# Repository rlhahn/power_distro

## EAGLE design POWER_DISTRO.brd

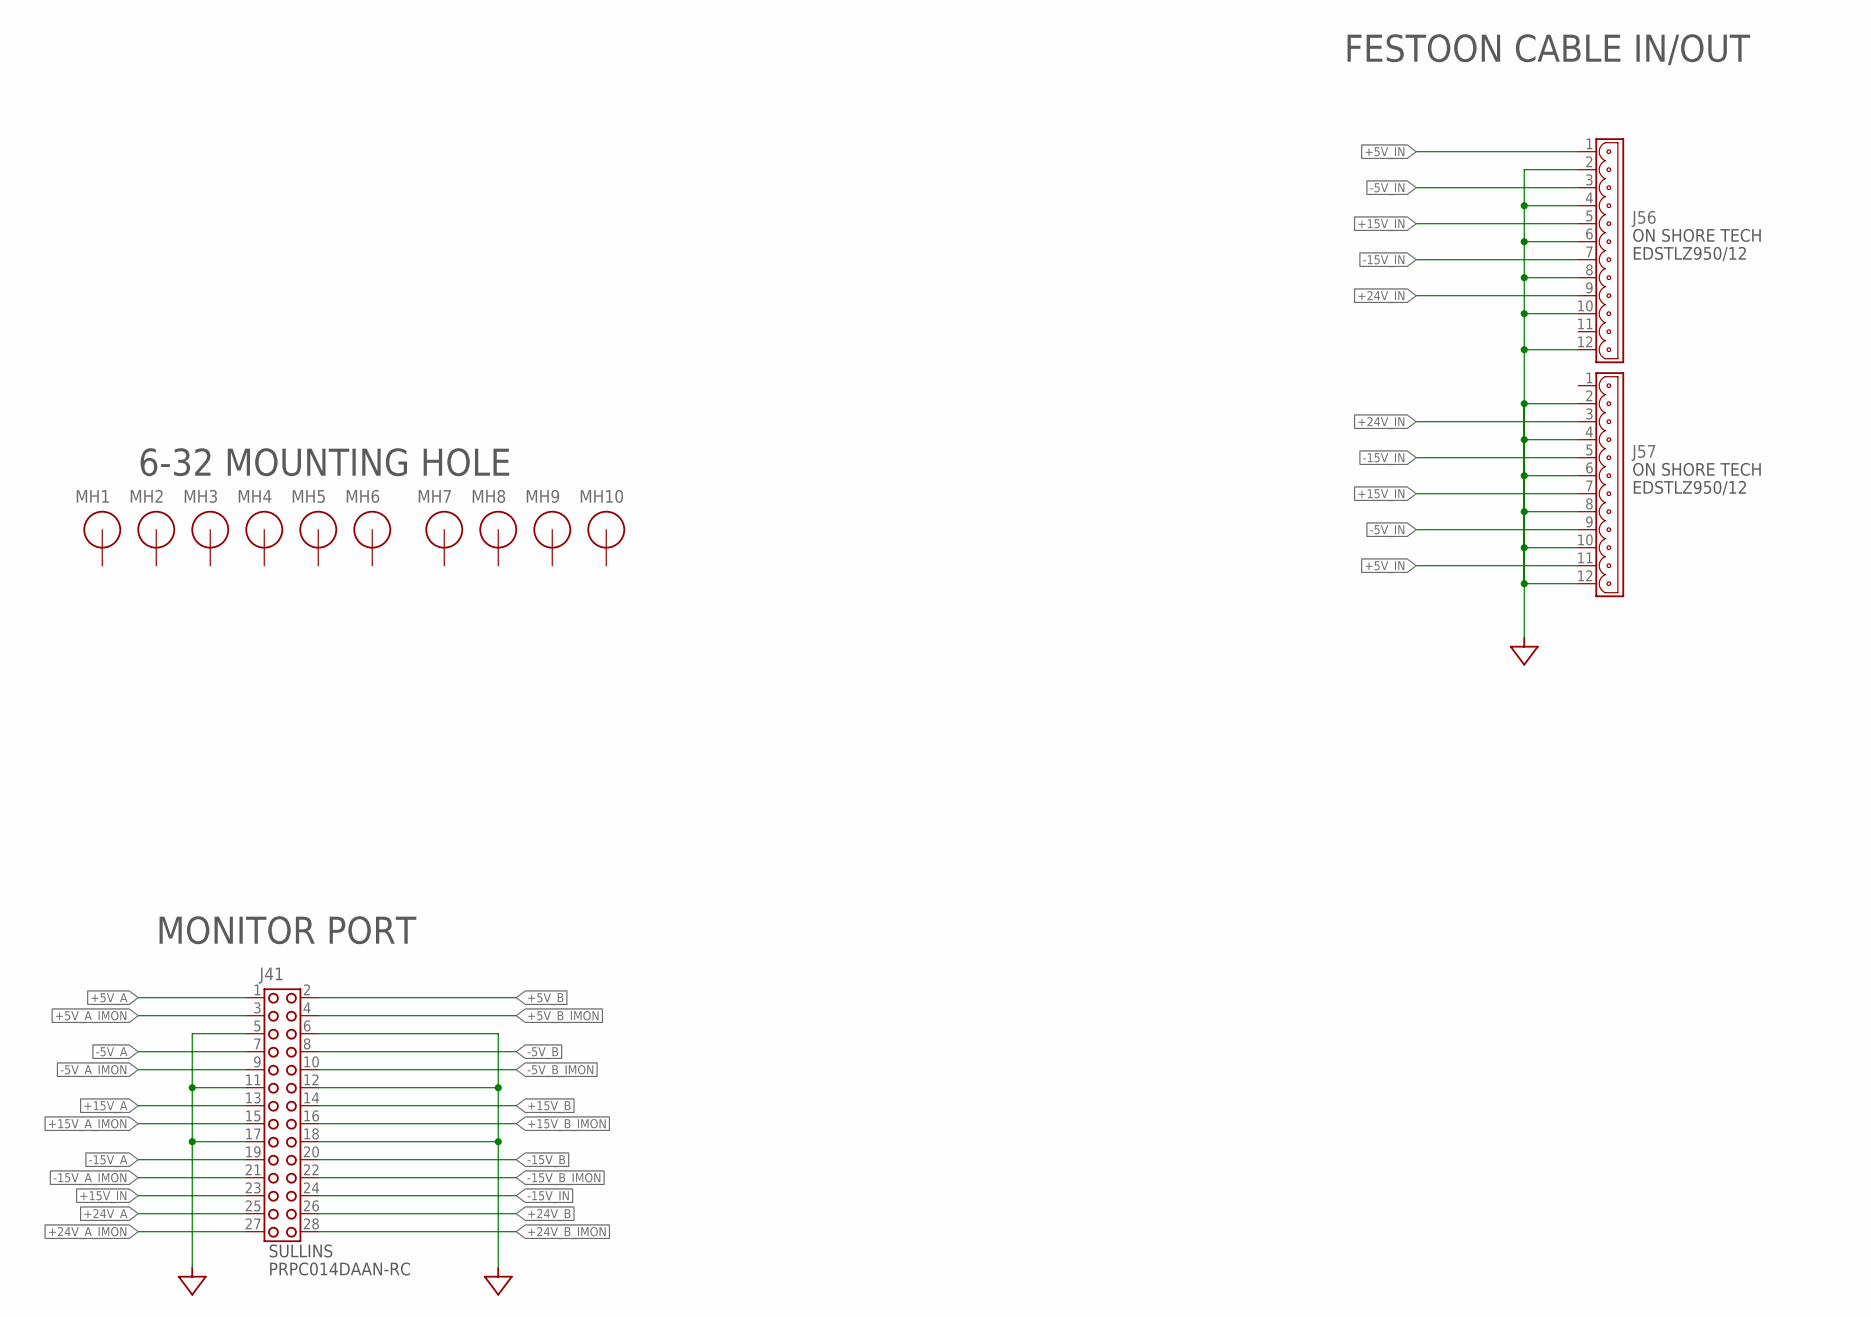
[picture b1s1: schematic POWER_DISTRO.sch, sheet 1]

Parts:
J41: HDR_2X14X100; 2X14X0.100_HDR
J56, J57: CONN_SCREWTERM_5.08MM_12POS; OST_OSTTJ125153
MH1, MH2, MH3, MH4, MH5, MH6, MH7, MH8, MH9, MH10: MTG-HOLE-6-32; MTG-6-32

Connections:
+5V_A: J41.1; also elsewhere on the board
+5V_A_IMON: J41.3; also elsewhere on the board
+5V_B: J41.2; also elsewhere on the board
+5V_B_IMON: J41.4; also elsewhere on the board
+5V_IN: J56.1, J57.11; also elsewhere on the board
+15V_A: J41.13; also elsewhere on the board
+15V_A_IMON: J41.15; also elsewhere on the board
+15V_B: J41.14; also elsewhere on the board
+15V_B_IMON: J41.16; also elsewhere on the board
+15V_IN: J41.23, J56.5, J57.7; also elsewhere on the board
+24V_A: J41.25; also elsewhere on the board
+24V_A_IMON: J41.27; also elsewhere on the board
+24V_B: J41.26; also elsewhere on the board
+24V_B_IMON: J41.28; also elsewhere on the board
+24V_IN: J56.9, J57.3; also elsewhere on the board
-5V_A: J41.7; also elsewhere on the board
-5V_A_IMON: J41.9; also elsewhere on the board
-5V_B: J41.8; also elsewhere on the board
-5V_B_IMON: J41.10; also elsewhere on the board
-5V_IN: J56.3, J57.9; also elsewhere on the board
-15V_A: J41.19; also elsewhere on the board
-15V_A_IMON: J41.21; also elsewhere on the board
-15V_B: J41.20; also elsewhere on the board
-15V_B_IMON: J41.22; also elsewhere on the board
-15V_IN: J41.24, J56.7, J57.5; also elsewhere on the board
AGND: J41.5, J41.6, J41.11, J41.12, J41.17, J41.18, J56.2, J56.4, J56.6, J56.8, J56.10, J56.12, J57.2, J57.4, J57.6, J57.8, J57.10, J57.12; also elsewhere on the board

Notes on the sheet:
6-32 MOUNTING HOLE
MONITOR PORT
FESTOON CABLE IN/OUT

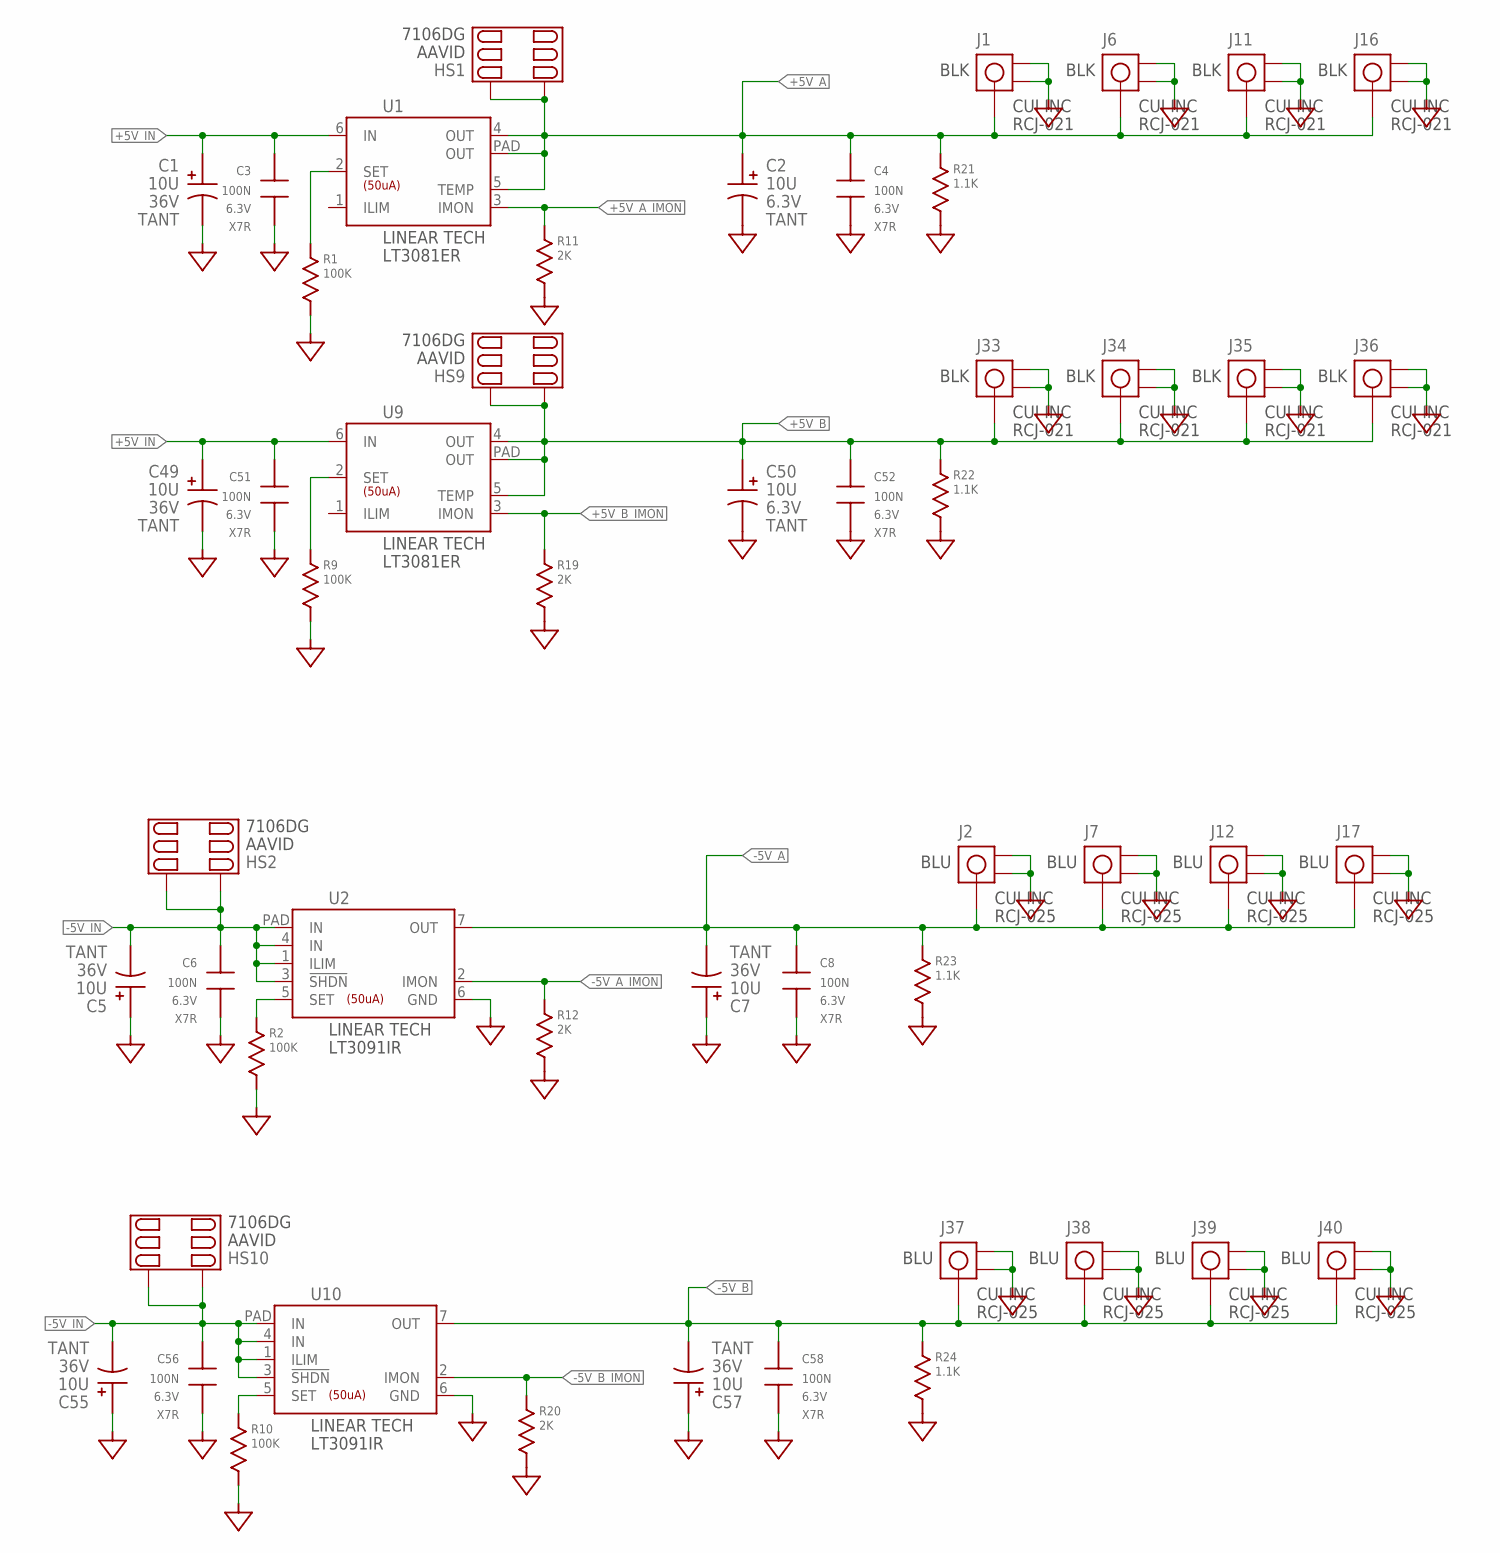
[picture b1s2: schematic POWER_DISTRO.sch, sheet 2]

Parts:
C1, C5, C7, C49, C55, C57: 10U; CAP-SIZE_D/E_EIA7343; VOLTAGE 36V
C2, C50: 10U; CAP-SIZE_D/E_EIA7343
C3, C4, C6, C8, C51, C52, C56, C58: 100N; R-0805
HS1, HS2, HS9, HS10: HEATSINK_AAVID_7106; AAVID_7106
J1, J2, J6, J7, J11, J12, J16, J17, J33, J34, J35, J36, J37, J38, J39, J40: CONN_RCA; CUI_RCJ-02X
R1, R2, R9, R10: 100K; R-0805
R11, R12, R20: 2K; R-0805
R19: 2K; R-0805; TOLERANCE 1%
R21, R22, R23, R24: 1.1K; R-0805
U1, U9: REG_LT3081; DD-7_LINEARTECH
U2, U10: REG_LT3091; DD-7_LINEARTECH

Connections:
+5V_A: C2.+, C4.A, HS1.L, HS1.R, J1.PIN, J6.PIN, J11.PIN, J16.PIN, R21.A, U1.4 (OUT), U1.5 (TEMP), U1.PAD (OUT); also elsewhere on the board
+5V_A_IMON: R11.A, U1.3 (IMON); also elsewhere on the board
+5V_B: C50.+, C52.A, HS9.L, HS9.R, J33.PIN, J34.PIN, J35.PIN, J36.PIN, R22.A, U9.4 (OUT), U9.5 (TEMP), U9.PAD (OUT); also elsewhere on the board
+5V_B_IMON: R19.A, U9.3 (IMON); also elsewhere on the board
+5V_IN: C1.+, C3.A, C49.+, C51.A, U1.6 (IN), U9.6 (IN); also elsewhere on the board
-5V_A: C7.-, C8.A, J2.PIN, J7.PIN, J12.PIN, J17.PIN, R23.A, U2.7 (OUT); also elsewhere on the board
-5V_A_IMON: R12.A, U2.2 (IMON); also elsewhere on the board
-5V_B: C57.-, C58.A, J37.PIN, J38.PIN, J39.PIN, J40.PIN, R24.A, U10.7 (OUT); also elsewhere on the board
-5V_B_IMON: R20.A, U10.2 (IMON); also elsewhere on the board
-5V_IN: C5.-, C6.A, C55.-, C56.A, HS2.L, HS2.R, HS10.L, HS10.R, U2.1 (ILIM), U2.3 (!SHDN), U2.4 (IN), U2.PAD (IN), U10.1 (ILIM), U10.3 (!SHDN), U10.4 (IN), U10.PAD (IN); also elsewhere on the board
AGND: C1.-, C2.-, C3.B, C4.B, C5.+, C6.B, C7.+, C8.B, C49.-, C50.-, C51.B, C52.B, C55.+, C56.B, C57.+, C58.B, J1.GND@1, J1.GND@2, J2.GND@1, J2.GND@2, J6.GND@1, J6.GND@2, J7.GND@1, J7.GND@2, J11.GND@1, J11.GND@2, J12.GND@1, J12.GND@2, J16.GND@1, J16.GND@2, J17.GND@1, J17.GND@2, J33.GND@1, J33.GND@2, J34.GND@1, J34.GND@2, J35.GND@1, J35.GND@2, J36.GND@1, J36.GND@2, J37.GND@1, J37.GND@2, J38.GND@1, J38.GND@2, J39.GND@1, J39.GND@2, J40.GND@1, J40.GND@2, R1.B, R2.B, R9.B, R10.B, R11.B, R12.B, R19.B, R20.B, R21.B, R22.B, R23.B, R24.B, U2.6 (GND), U10.6 (GND); also elsewhere on the board
unnamed: R1.A, U1.2 (SET)
unnamed: R2.A, U2.5 (SET)
unnamed: R9.A, U9.2 (SET)
unnamed: R10.A, U10.5 (SET)

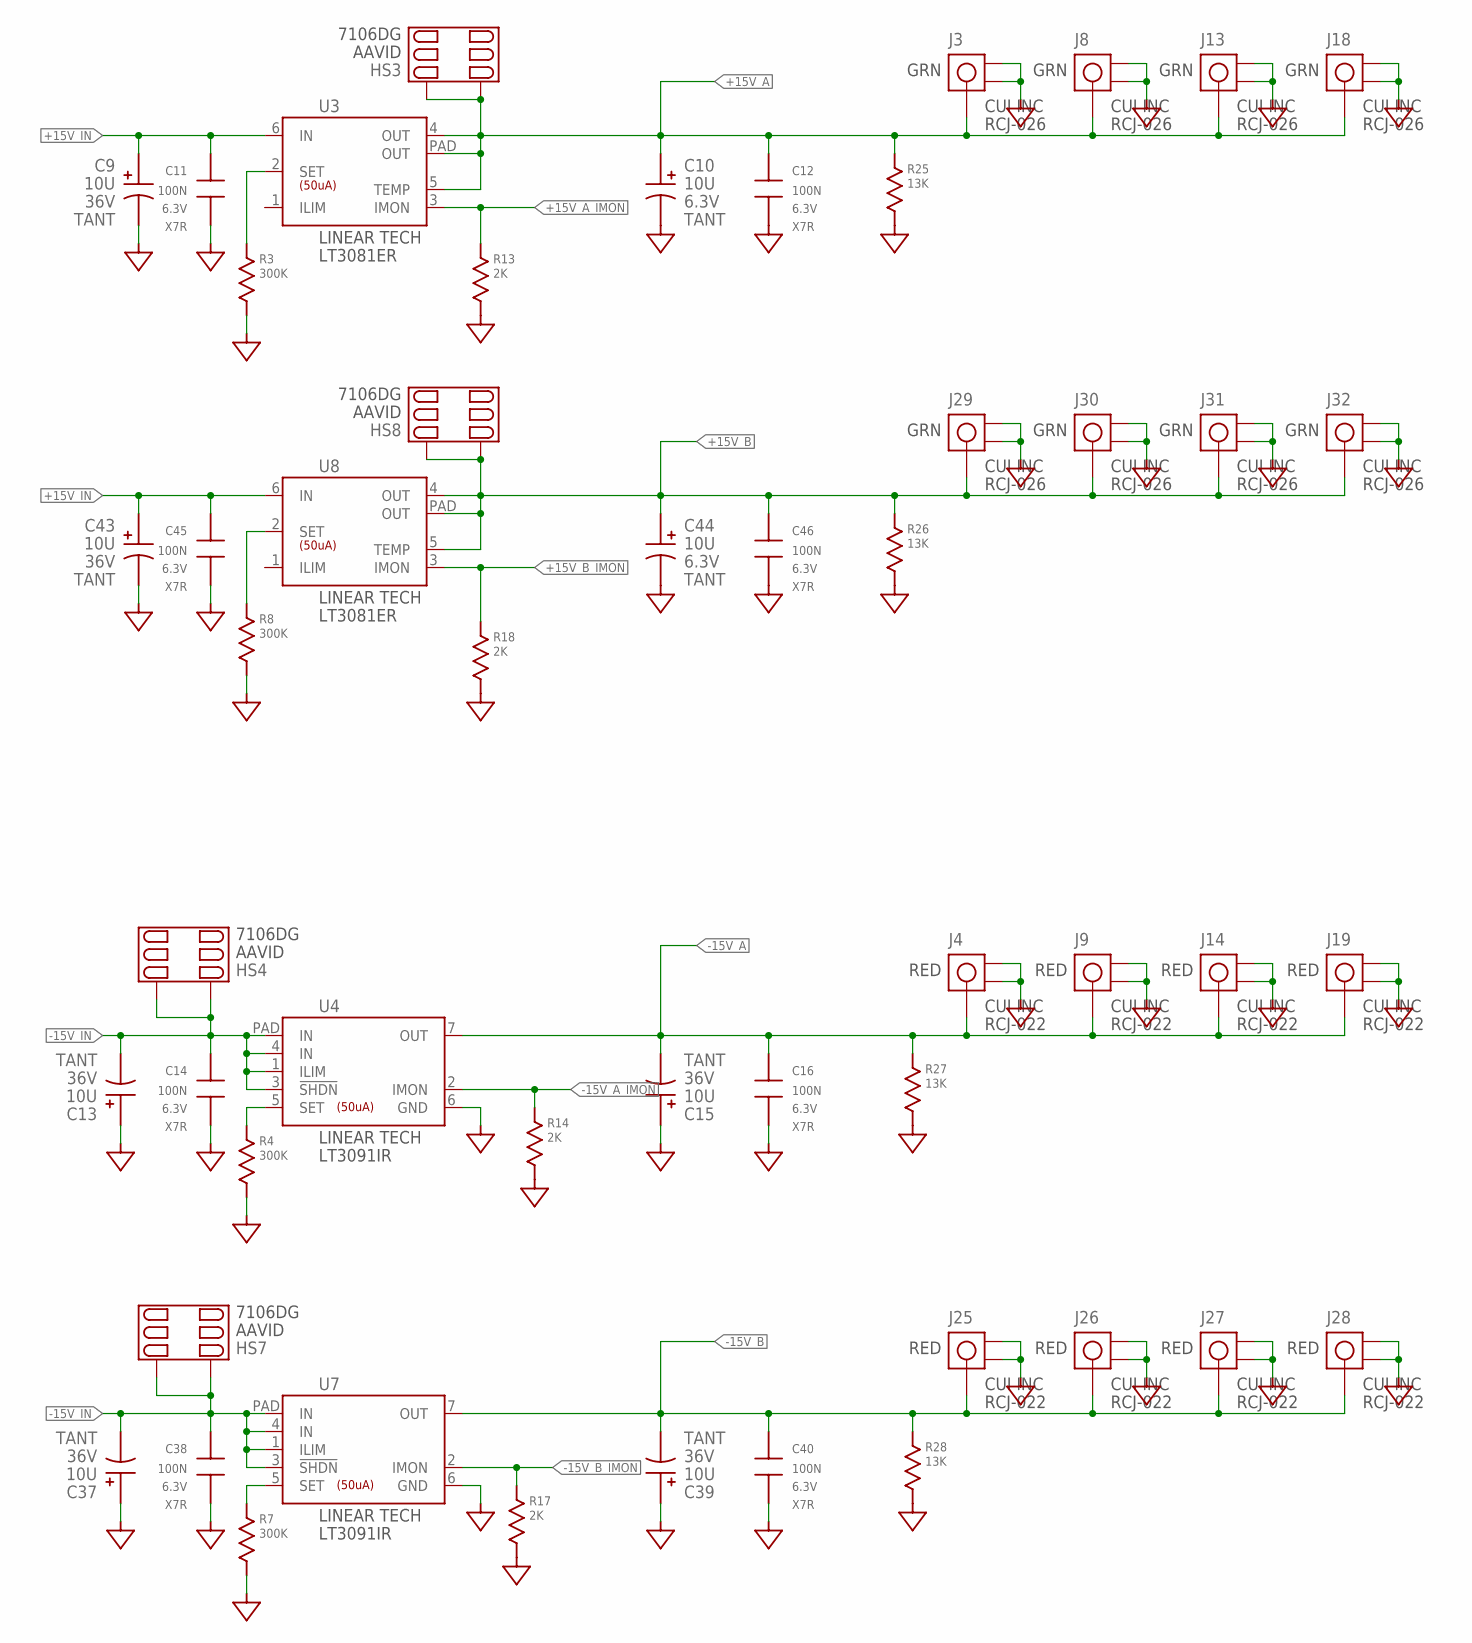
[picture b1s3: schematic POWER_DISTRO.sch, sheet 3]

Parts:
C9, C13, C15, C37, C39, C43: 10U; CAP-SIZE_D/E_EIA7343; VOLTAGE 36V
C10, C44: 10U; CAP-SIZE_D/E_EIA7343
C11, C12, C14, C16, C38, C40, C45, C46: 100N; R-0805
HS3, HS4, HS7, HS8: HEATSINK_AAVID_7106; AAVID_7106
J3, J4, J8, J9, J13, J14, J18, J19, J25, J26, J27, J28, J29, J30, J31, J32: CONN_RCA; CUI_RCJ-02X
R3, R4, R7, R8: 300K; R-0805
R13, R14, R17, R18: 2K; R-0805; TOLERANCE 1%
R25, R26, R27, R28: 13K; R-0805; TOLERANCE 1%
U3, U8: REG_LT3081; DD-7_LINEARTECH
U4, U7: REG_LT3091; DD-7_LINEARTECH

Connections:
+15V_A: C10.+, C12.A, HS3.L, HS3.R, J3.PIN, J8.PIN, J13.PIN, J18.PIN, R25.A, U3.4 (OUT), U3.5 (TEMP), U3.PAD (OUT); also elsewhere on the board
+15V_A_IMON: R13.A, U3.3 (IMON); also elsewhere on the board
+15V_B: C44.+, C46.A, HS8.L, HS8.R, J29.PIN, J30.PIN, J31.PIN, J32.PIN, R26.A, U8.4 (OUT), U8.5 (TEMP), U8.PAD (OUT); also elsewhere on the board
+15V_B_IMON: R18.A, U8.3 (IMON); also elsewhere on the board
+15V_IN: C9.+, C11.A, C43.+, C45.A, U3.6 (IN), U8.6 (IN); also elsewhere on the board
-15V_A: C15.-, C16.A, J4.PIN, J9.PIN, J14.PIN, J19.PIN, R27.A, U4.7 (OUT); also elsewhere on the board
-15V_A_IMON: R14.A, U4.2 (IMON); also elsewhere on the board
-15V_B: C39.-, C40.A, J25.PIN, J26.PIN, J27.PIN, J28.PIN, R28.A, U7.7 (OUT); also elsewhere on the board
-15V_B_IMON: R17.A, U7.2 (IMON); also elsewhere on the board
-15V_IN: C13.-, C14.A, C37.-, C38.A, HS4.L, HS4.R, HS7.L, HS7.R, U4.1 (ILIM), U4.3 (!SHDN), U4.4 (IN), U4.PAD (IN), U7.1 (ILIM), U7.3 (!SHDN), U7.4 (IN), U7.PAD (IN); also elsewhere on the board
AGND: C9.-, C10.-, C11.B, C12.B, C13.+, C14.B, C15.+, C16.B, C37.+, C38.B, C39.+, C40.B, C43.-, C44.-, C45.B, C46.B, J3.GND@1, J3.GND@2, J4.GND@1, J4.GND@2, J8.GND@1, J8.GND@2, J9.GND@1, J9.GND@2, J13.GND@1, J13.GND@2, J14.GND@1, J14.GND@2, J18.GND@1, J18.GND@2, J19.GND@1, J19.GND@2, J25.GND@1, J25.GND@2, J26.GND@1, J26.GND@2, J27.GND@1, J27.GND@2, J28.GND@1, J28.GND@2, J29.GND@1, J29.GND@2, J30.GND@1, J30.GND@2, J31.GND@1, J31.GND@2, J32.GND@1, J32.GND@2, R3.B, R4.B, R7.B, R8.B, R13.B, R14.B, R17.B, R18.B, R25.B, R26.B, R27.B, R28.B, U4.6 (GND), U7.6 (GND); also elsewhere on the board
unnamed: R3.A, U3.2 (SET)
unnamed: R4.A, U4.5 (SET)
unnamed: R7.A, U7.5 (SET)
unnamed: R8.A, U8.2 (SET)

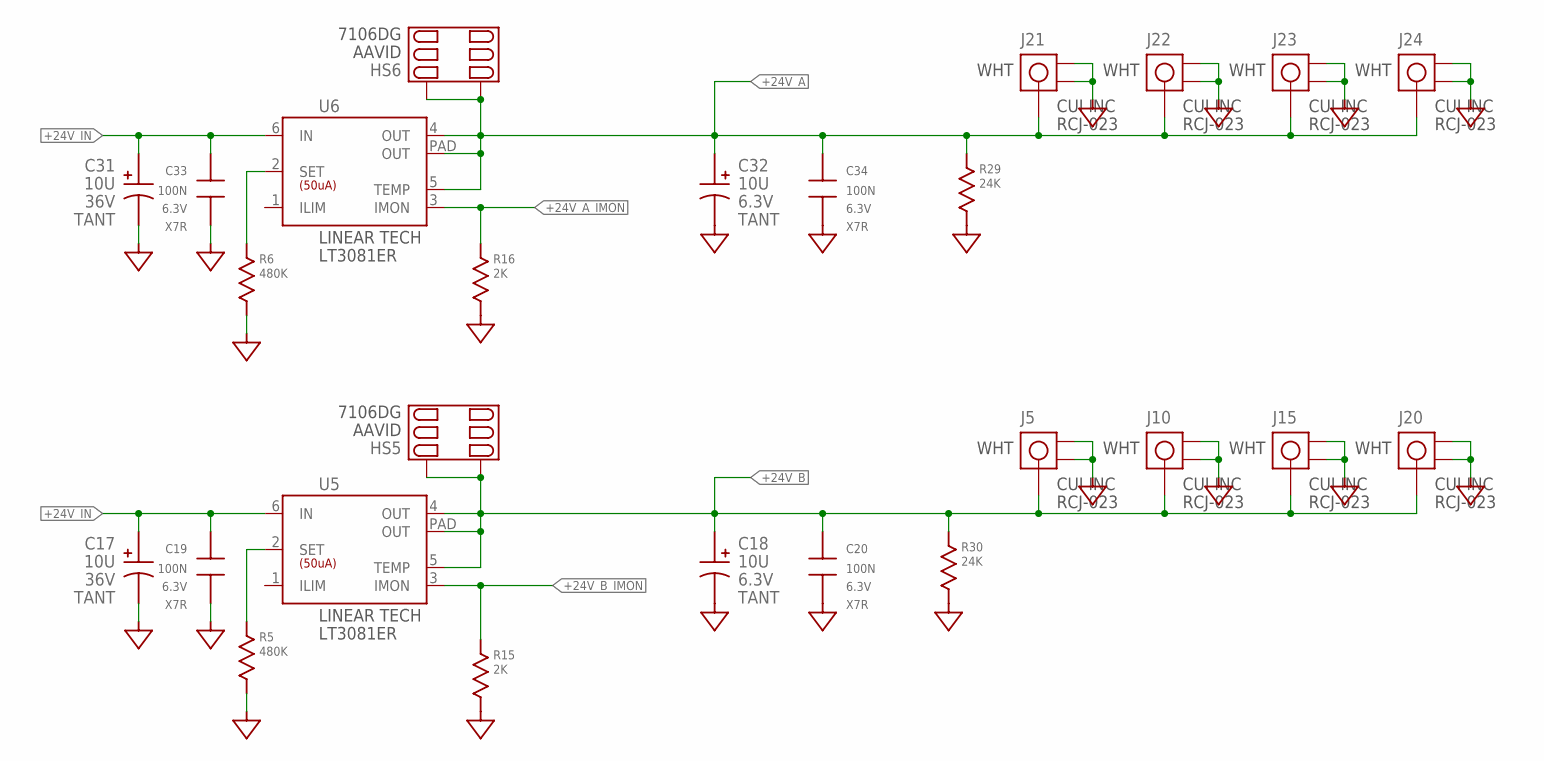
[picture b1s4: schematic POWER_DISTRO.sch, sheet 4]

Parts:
C17, C31: 10U; CAP-SIZE_D/E_EIA7343; VOLTAGE 36V
C18, C32: 10U; CAP-SIZE_D/E_EIA7343
C19, C20, C33, C34: 100N; R-0805
HS5, HS6: HEATSINK_AAVID_7106; AAVID_7106
J5, J10, J15, J20, J21, J22, J23, J24: CONN_RCA; CUI_RCJ-02X
R5, R6: 480K; R-0805
R15, R16: 2K; R-0805; TOLERANCE 1%
R29, R30: 24K; R-0805; TOLERANCE 1%
U5, U6: REG_LT3081; DD-7_LINEARTECH

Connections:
+24V_A: C32.+, C34.A, HS6.L, HS6.R, J21.PIN, J22.PIN, J23.PIN, J24.PIN, R29.A, U6.4 (OUT), U6.5 (TEMP), U6.PAD (OUT); also elsewhere on the board
+24V_A_IMON: R16.A, U6.3 (IMON); also elsewhere on the board
+24V_B: C18.+, C20.A, HS5.L, HS5.R, J5.PIN, J10.PIN, J15.PIN, J20.PIN, R30.A, U5.4 (OUT), U5.5 (TEMP), U5.PAD (OUT); also elsewhere on the board
+24V_B_IMON: R15.A, U5.3 (IMON); also elsewhere on the board
+24V_IN: C17.+, C19.A, C31.+, C33.A, U5.6 (IN), U6.6 (IN); also elsewhere on the board
AGND: C17.-, C18.-, C19.B, C20.B, C31.-, C32.-, C33.B, C34.B, J5.GND@1, J5.GND@2, J10.GND@1, J10.GND@2, J15.GND@1, J15.GND@2, J20.GND@1, J20.GND@2, J21.GND@1, J21.GND@2, J22.GND@1, J22.GND@2, J23.GND@1, J23.GND@2, J24.GND@1, J24.GND@2, R5.B, R6.B, R15.B, R16.B, R29.B, R30.B; also elsewhere on the board
unnamed: R5.A, U5.2 (SET)
unnamed: R6.A, U6.2 (SET)

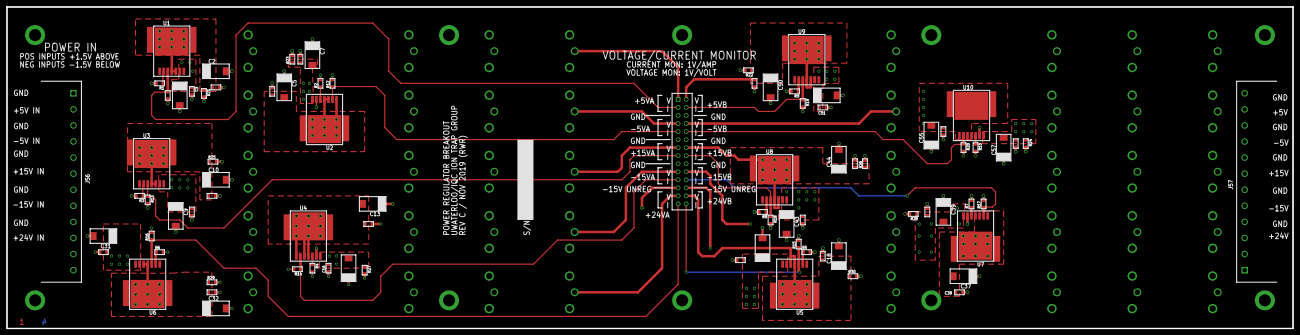
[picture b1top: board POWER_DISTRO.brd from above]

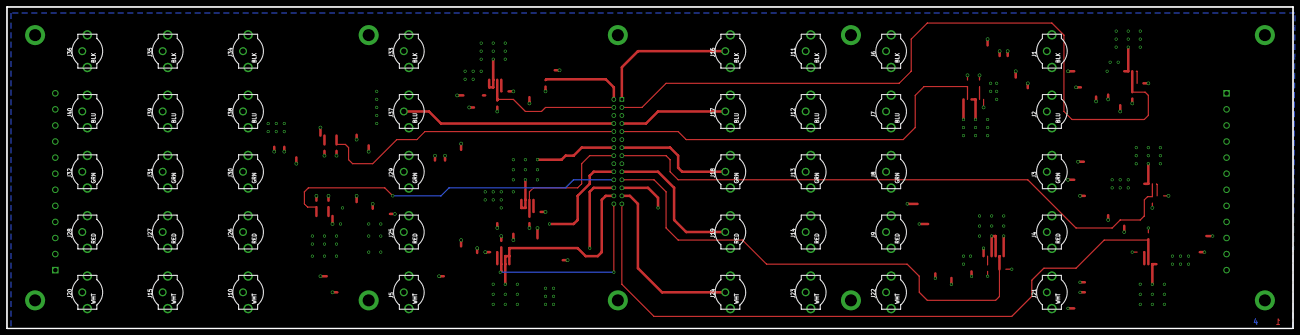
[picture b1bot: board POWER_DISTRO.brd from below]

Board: 4 copper layers, 406.4 x 101.6 mm, 143 parts (40 on the bottom side), 36 nets.

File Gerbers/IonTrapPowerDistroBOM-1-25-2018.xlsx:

Ion Trap Power Distro Box Bill Of Materials (1-25-2018)
QTY | REF | PACKAGE | VALUE | COLOR | COST | DIELECTRIC | MFG | MPN | PACKAGE | PRICE | TOLERANCE | VENDOR | VOLTAGE | VPN
14 | C1,C5,C7,C9,C13,C15,C17,C31,C37,C39,C43,C49,C55,C57, | CAP-SIZE_D/E_EIA7343 | 10U |  | 1.5 | TANT | AVX | TAJD-SERIES |  |  |  | DIGIKEY | 36V
6 | C2,C10,C18,C32,C44,C50, | CAP-SIZE_D/E_EIA7343 | 10U |  | 1.5 | TANT | AVX | TAJD-SERIES |  |  |  | DIGIKEY | 6.3V
20 | C3,C4,C6,C8,C11,C12,C14,C16,C19,C20,C33,C34,C38,C40,C45,C46,C51,C52,C56,C58, | R-0805 | 100N |  | 7.3999999999999996E-2 | X7R |  |  |  |  |  |  | 6.3V
10 | HS1,HS2,HS3,HS4,HS5,HS6,HS7,HS8,HS9,HS10, | AAVID_7106 | HEATSINK_AAVID_7106 |  |  |  | AAVID | 7106DG |  | 1.44 |  | DIGIKEY |  | HS412-ND
8 | J1,J6,J11,J16,J33,J34,J35,J36, | CUI_RCJ-02X | CONN_RCA | BLK |  |  | CUI INC | RCJ-021 |  | 0.88 |  | DIGIKEY |  | CP-1406-ND
8 | J2,J7,J12,J17,J37,J38,J39,J40, | CUI_RCJ-02X | CONN_RCA | BLU |  |  | CUI INC | RCJ-025 |  | 0.88 |  | DIGIKEY |  | CP-1410-ND
8 | J3,J8,J13,J18,J29,J30,J31,J32, | CUI_RCJ-02X | CONN_RCA | GRN |  |  | CUI INC | RCJ-026 |  | 0.88 |  | DIGIKEY |  | CP-1411-ND
8 | J4,J9,J14,J19,J25,J26,J27,J28, | CUI_RCJ-02X | CONN_RCA | RED |  |  | CUI INC | RCJ-022 |  | 0.88 |  | DIGIKEY |  | CP-1407-ND
8 | J5,J10,J15,J20,J21,J22,J23,J24, | CUI_RCJ-02X | CONN_RCA | WHT |  |  | CUI INC | RCJ-023 |  | 0.88 |  | DIGIKEY |  | CP-1408-ND
1 | J41, | 2X14X0.100_HDR | HDR_2X14X100 |  |  |  | SULLINS | PRPC014DAAN-RC |  | 1 |  | DIGIKEY |  | S2011EC-14-ND
6 | J46,J47,J48,J49,J50,J51, | OST_SCREWTERM_3.5MM_2POS | CONN_SCREWTERM_3.5MM_2POS |  |  |  | ON SHORE TECH | OSTTE020161 |  | 0.92 |  | DIGIKEY |  | ED2635-ND
2 | R1,R2, | R-0805 | 100K |  |  |  |  |  | 805 | 5.8999999999999997E-2 | 0.01
4 | R3,R4,R7,R8, | R-0805 | 300K |  |  |  |  |  |  | 5.8999999999999997E-2
2 | R5,R6, | R-0805 | 480K |  |  |  |  |  |  | 5.8999999999999997E-2
2 | R9,R10, | R-0805 | 100K |  |  |  |  |  |  | 5.8999999999999997E-2
10 | R11,R12,R13,R14,R15,R16,R17,R18,R19,R20, | R-0805 | 2K |  |  |  |  |  | 805 | 5.8999999999999997E-2 | 0.01
6 | U1,U3,U5,U6,U8,U9, | DD-7_LINEARTECH | REG_LT3081 |  |  |  | LINEAR TECH | LT3081ER |  | 6.25 |  | DIGIKEY |  | LT3081ER#PBF-ND
4 | U2,U4,U7,U10, | DD-7_LINEARTECH | REG_LT3091 |  |  |  | LINEAR TECH | LT3091IR |  | 8.1199999999999992 |  | DIGIKEY |  | LT3091IR#PBF-ND

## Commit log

2018-02-18 as-builts Rev A
2018-03-08 Added Lab Power Distribution System Design.docx
2018-04-19 updates prior to rev B
2018-04-20 Rev B
2018-04-30 added subassembly parts
2018-05-01 Updates to enclosure
2018-05-02 Finished assembly
2018-05-11 Updated RevB inner
2018-06-26 Rev B checkin
2018-06-27 Created new BOM and gerbers and Solidmodels
2018-06-28 Redraw Enclosure to fit new Rev B board
2018-07-26 Gerbers committed to order REV B
2018-07-26 Enclosure design for purchase at xometry
2018-08-12 updates to eagle files
2018-09-24 ADDED PHOENIX CONTACT 1X12X3.5MM HEADER
2018-09-24 ADDED 3_5mm_5_08mm_adapter.sch
2018-09-24 ADDED DATASHEETS
2018-09-24 COMPLETED SCHEMATIC
2018-11-13 Updates to 3.5mm adaptor
2018-11-13 Updates for 3.5mm_to_5.08mm adapter. Updates to Inventor model accordingly. Added zip files for gerbers
2019-11-26 Commit to Rev C
